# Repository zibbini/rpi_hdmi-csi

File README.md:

# HDMI-CSI converter board for Raspberry Pi

A simple hdmi to csi converter board for 15 pin camera connectors used in Raspberry Pi hardware. 

Note that the track widths and layer thickness for controlled impedance was calculated with the following stack-up from JLCPCB: [JLC04161H-3313](https://jlcpcb.com/impedance), so you will need to specify this when ordering via JLC. 

Complete gerbers, drill files, BOM and CPL are also included in `/manufacturing` if you just want to order this board without checking out the design.

## Support 

For questions, issues or suggestions please open an issue in the Github repository.

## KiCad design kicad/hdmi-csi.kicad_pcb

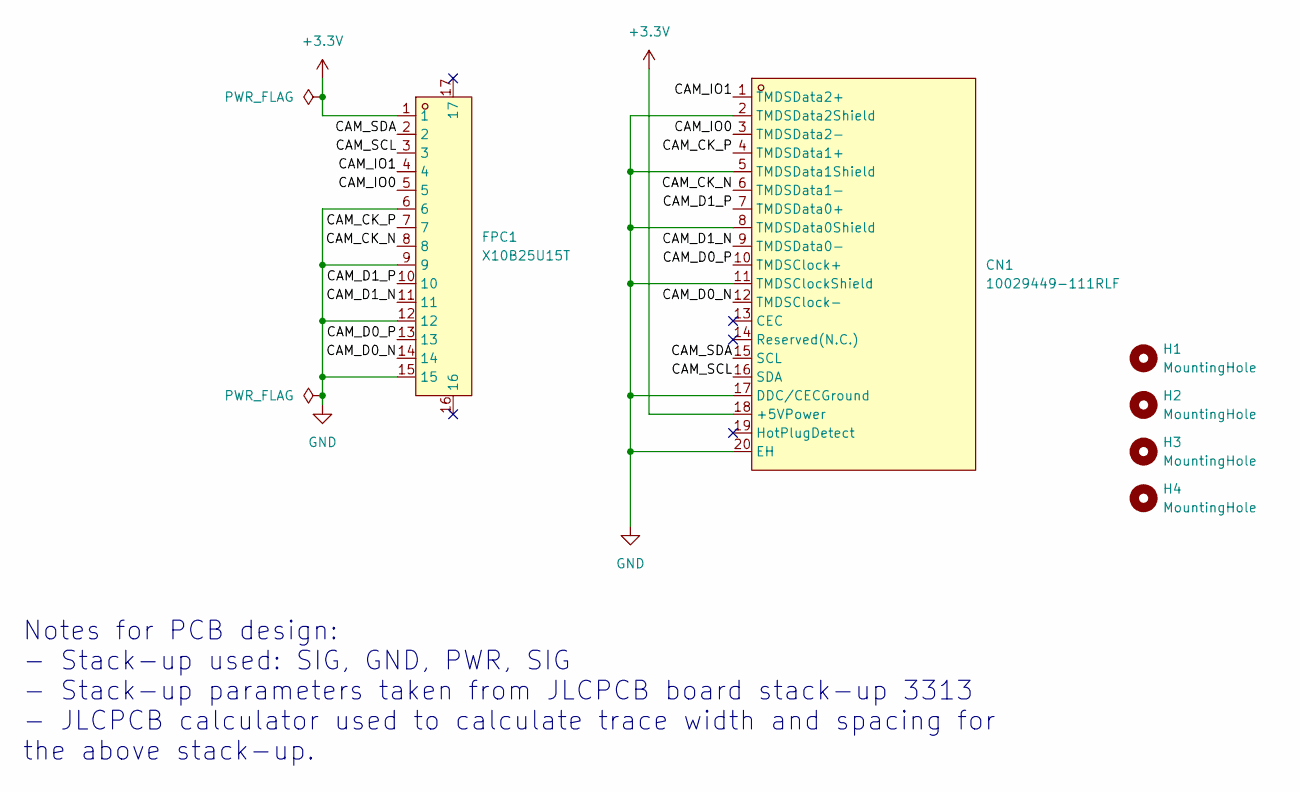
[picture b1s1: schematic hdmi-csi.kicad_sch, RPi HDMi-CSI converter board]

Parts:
CN1: 10029449-111RLF; HDMI-SMD_10029449-001RLF; LCSC Part C427307
FPC1: X10B25U15T; FPC-SMD_X10B25U15T; LCSC Part C500193
H1, H2, H3, H4: MountingHole; MountingHole_2.1mm

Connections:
+3.3V: CN1.18 (+5VPower), FPC1.1
/CAM_CK_N: CN1.6 (TMDSData1-), FPC1.8
/CAM_CK_P: CN1.4 (TMDSData1+), FPC1.7
/CAM_D0_N: CN1.12 (TMDSClock-), FPC1.14
/CAM_D0_P: CN1.10 (TMDSClock+), FPC1.13
/CAM_D1_N: CN1.9 (TMDSData0-), FPC1.11
/CAM_D1_P: CN1.7 (TMDSData0+), FPC1.10
/CAM_IO0: CN1.3 (TMDSData2-), FPC1.5
/CAM_IO1: CN1.1 (TMDSData2+), FPC1.4
/CAM_SCL: CN1.16 (SDA), FPC1.3
/CAM_SDA: CN1.15 (SCL), FPC1.2
GND: CN1.2 (TMDSData2Shield), CN1.5 (TMDSData1Shield), CN1.8 (TMDSData0Shield), CN1.11 (TMDSClockShield), CN1.17 (DDC/CECGround), CN1.20 (EH), FPC1.6, FPC1.9, FPC1.12, FPC1.15

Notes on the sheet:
Notes for PCB design: - Stack-up used: SIG, GND, PWR, SIG - Stack-up parameters taken from JLCPCB board stack-up 3313 - JLCPCB calculator used to calculate trace width and spacing for the above stack-up.

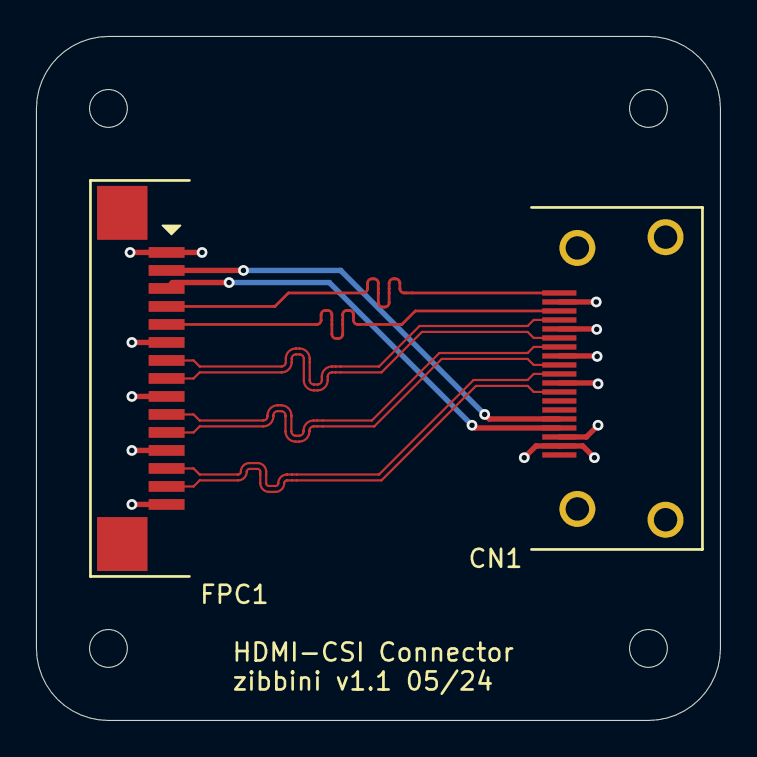
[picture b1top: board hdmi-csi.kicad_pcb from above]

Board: 4 copper layers, 38.0 x 38.0 mm, 6 parts (0 on the bottom side), 12 nets.

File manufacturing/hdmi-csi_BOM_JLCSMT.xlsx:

Comment | Designator | Footprint | JLCPCB Part #（optional）
10029449-111RLF | CN1 | HDMI-SMD_10029449-001RLF | C427307
X10B25U15T | FPC1 | FPC-SMD_X10B25U15T | C500193

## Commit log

2024-06-18 Initial commit.
2024-06-18 Remove files.
2024-06-26 Update README.
2024-06-26 Replace files.
2024-06-26 Fix link.
2024-06-26 Add license
2024-06-26 Add additional details.
